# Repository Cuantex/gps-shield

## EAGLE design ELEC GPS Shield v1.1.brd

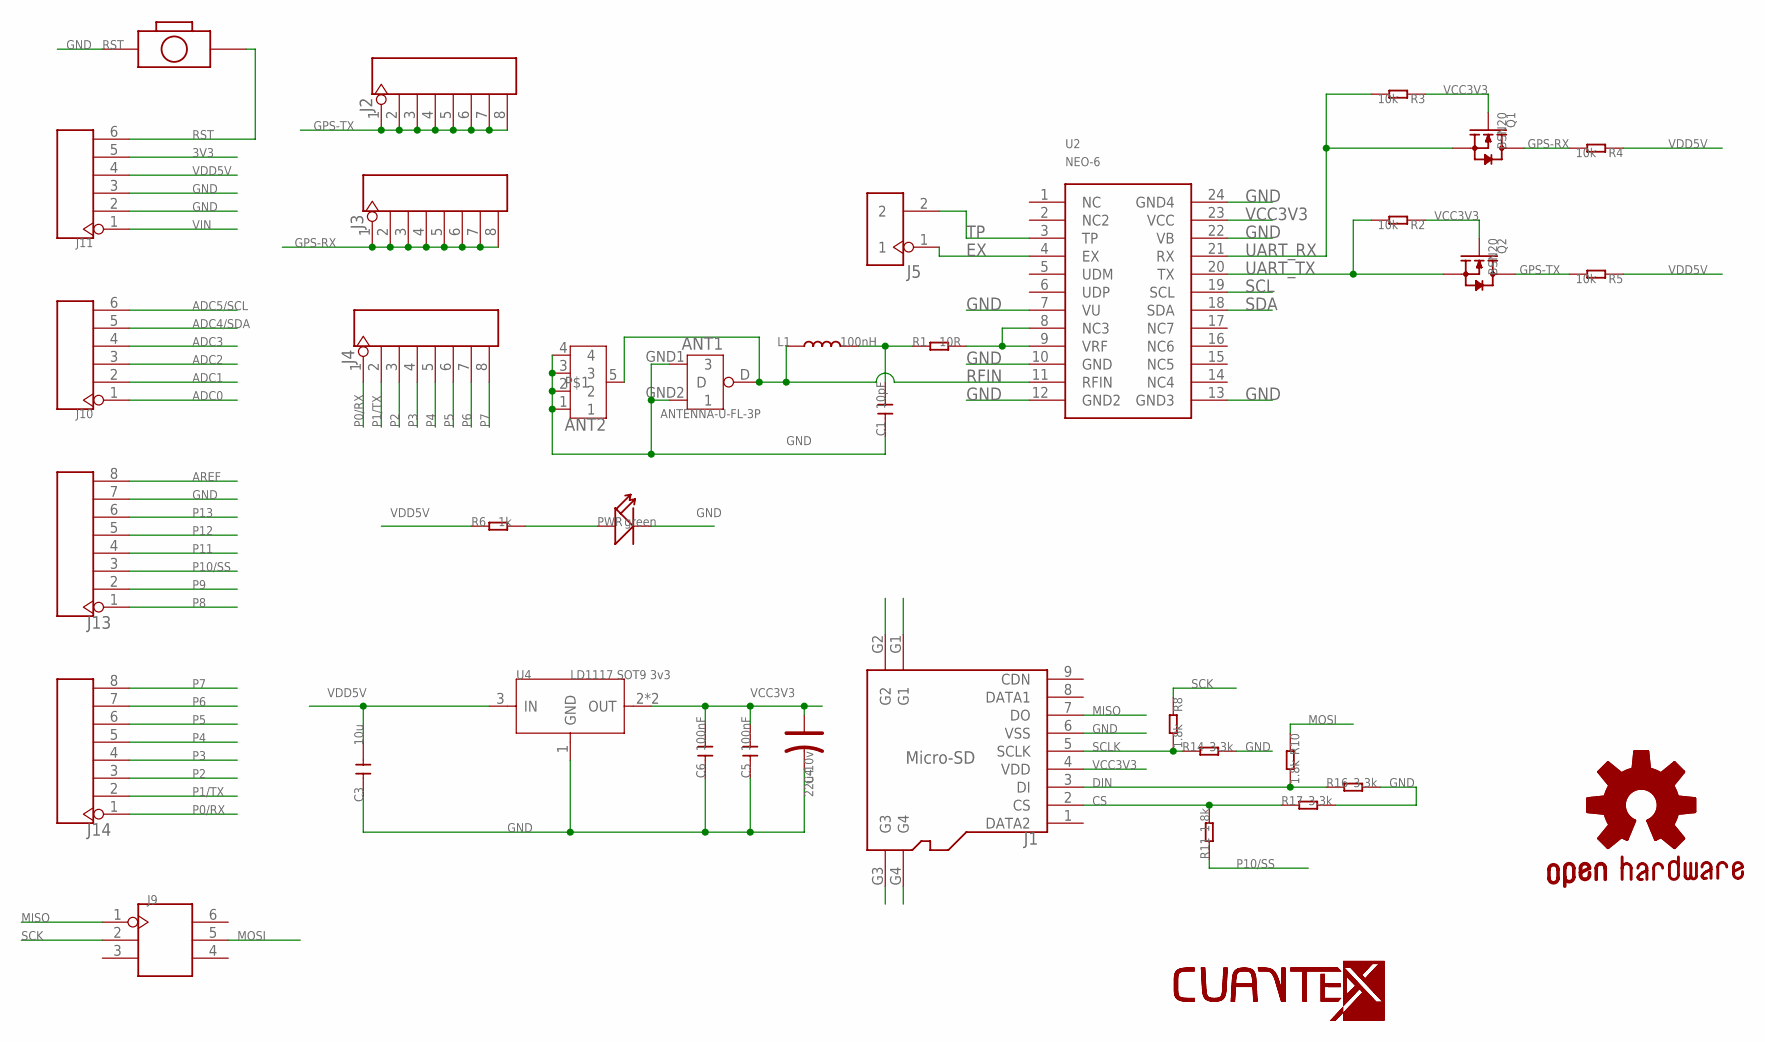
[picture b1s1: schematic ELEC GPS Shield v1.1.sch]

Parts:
ANT1: ANTENNA-U-FL-3P; 3P-U-FL
ANT2: ANTENNA-SMA-IPX; SMA-TO-IPX
C1: 10pF; C0603
C3: 10u; C0805
C4: 22u-10v; AVX-B
C5, C6: 100nF; C0603
GOLD_ORB_SM1: OSHWLOGO_GOLD_ORB_SM; OSHW2
J1: Micro-SD; 9P-SMD-W/-RING
J2, J3, J4, J13, J14: HEADER-8P-65/35MIL; 8P-2.54-65/35MIL
J5: HEADER-2P-65/35MIL; 2P-2.54-65/35MIL
J9: HEADER-2X3P-65/35MIL; 2X3P-2.54-65/35MIL
J10, J11: HEADER-6P-60/35MIL; 6P-2.54-60/35MIL
L1: 100nH; L0603
PWR: green; LED-0603
Q1, Q2: BSN20; SOT23
R1: 10R; R0603
R2, R3, R4, R5: 10k; R0603
R6: 1k; R0603
R8, R10, R11: 1.8k; R0603
R14, R16, R17: 3.3k; R0603
RST: BOTTON-2P-90D; 2P-7.62X3.56-90D
U2: NEO-6
U4: LD1117 SOT9 3v3; SOT89
U$1: LOGO-BOT-40MM; B-40
U$3: LOGO-TOP-20MM; C-0

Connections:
3V3: J11.5
ADC0: J10.1
ADC1: J10.2
ADC2: J10.3
ADC3: J10.4
ADC4/SDA: J10.5
ADC5/SCL: J10.6
AREF: J13.8
CS: J1.2 (CS), R11.2, R17.1
DIN: J1.3 (DI), R10.2, R16.1
EX: J5.1, U2.4 (EX)
GND: ANT1.GND1 (3), ANT1.GND2 (1), ANT2.1, ANT2.2, ANT2.3, ANT2.4, C1.1, C3.2, C4.-, C5.1, C6.1, J1.6 (VSS), J11.2, J11.3, J13.7, PWR.-, R14.2, R16.2, R17.2, RST.P$1 (1), U2.7 (VU), U2.10 (GND), U2.12 (GND2), U2.13 (GND3), U2.22 (VB), U2.24 (GND4), U4.1 (GND)
GPS-RX: J3.1, J3.2, J3.3, J3.4, J3.5, J3.6, J3.7, J3.8, Q1.3 (D), R4.2
GPS-TX: J2.1, J2.2, J2.3, J2.4, J2.5, J2.6, J2.7, J2.8, Q2.3 (D), R5.2
MISO: J1.7 (DO), J9.1
MOSI: J9.5, R10.1
unnamed: PWR.+, R6.2
unnamed: R1.2, U2.8 (NC3), U2.9 (VRF)
unnamed: C1.2, L1.2, R1.1
P0/RX: J4.1, J14.1
P1/TX: J4.2, J14.2
P2: J4.3, J14.3
P3: J4.4, J14.4
P4: J4.5, J14.5
P5: J4.6, J14.6
P6: J4.7, J14.7
P7: J4.8, J14.8
P8: J13.1
P9: J13.2
P10/SS: J13.3, R11.1
P11: J13.4
P12: J13.5
P13: J13.6
RFIN: ANT1.D, ANT2.5, L1.1, U2.11 (RFIN)
RST: J11.6, RST.P$2 (2)
SCK: J9.2, R8.1
SCL: U2.19 (SCL)
SCLK: J1.5 (SCLK), R8.2, R14.1
SDA: U2.18 (SDA)
TP: J5.2, U2.3 (TP)
UART_RX: Q1.2 (S), R3.2, U2.21 (RX)
UART_TX: Q2.2 (S), R2.2, U2.20 (TX)
VCC3V3: C4.+, C5.2, C6.2, J1.4 (VDD), Q1.1 (G), Q2.1 (G), R2.1, R3.1, U2.23 (VCC), U4.2 (OUT), U4.4 (OUT)
VDD5V: C3.1, J11.4, R4.1, R5.1, R6.1, U4.3 (IN)
VIN: J11.1

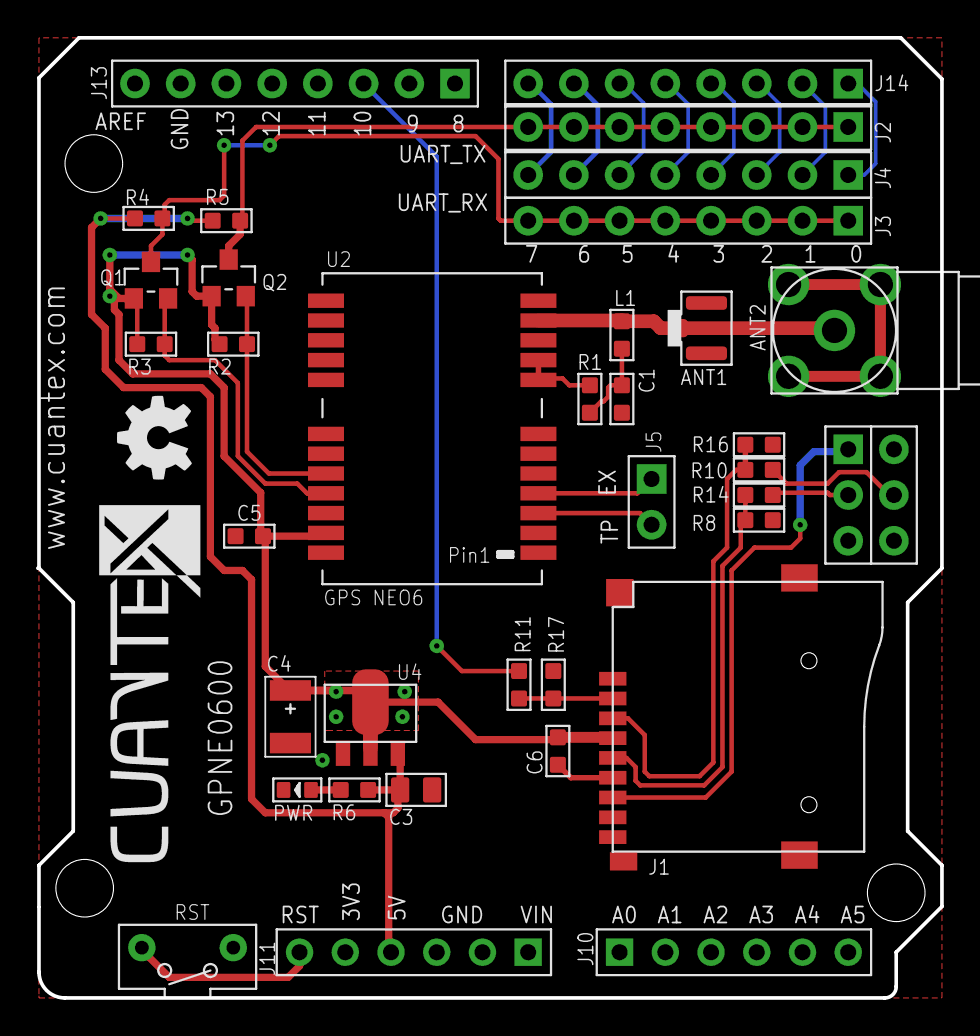
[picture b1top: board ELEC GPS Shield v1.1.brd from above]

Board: 2 copper layers, 50.2 x 53.3 mm, 39 parts (0 on the bottom side), 29 nets.

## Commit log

2016-03-23 Archivos en Git
